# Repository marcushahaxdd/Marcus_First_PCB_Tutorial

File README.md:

# Marcus_First_PCB_Tutorial
 first try pcb

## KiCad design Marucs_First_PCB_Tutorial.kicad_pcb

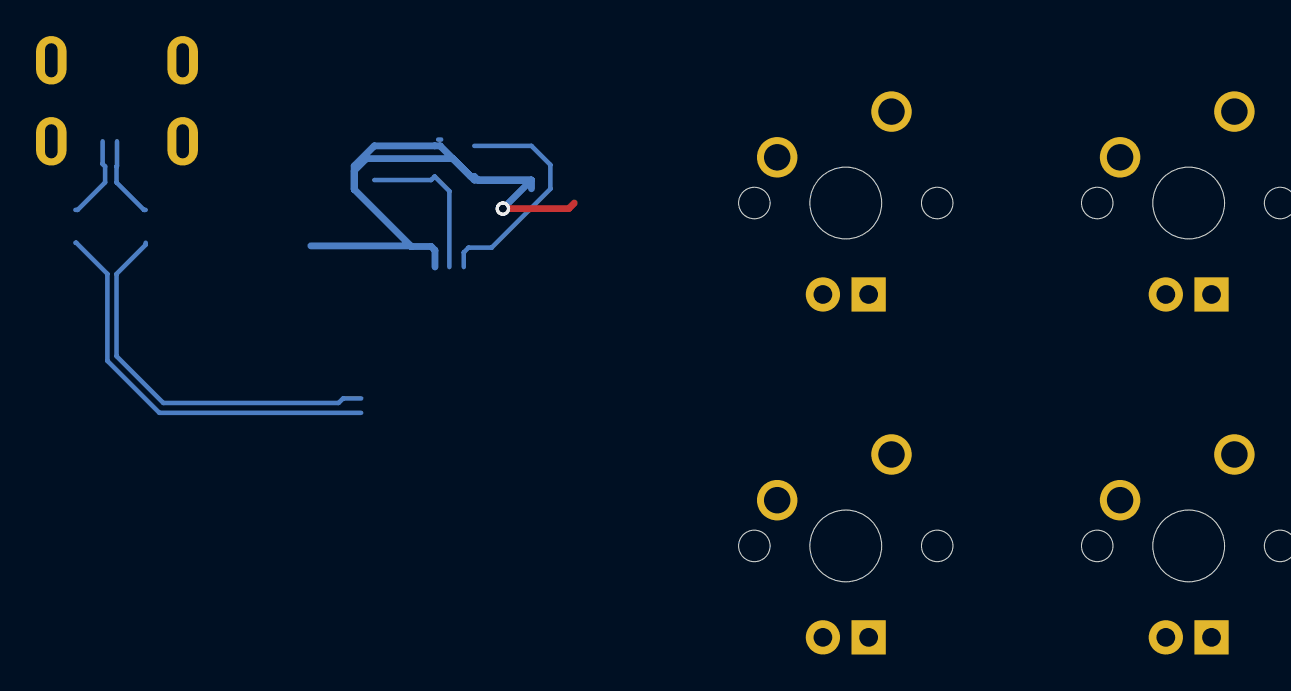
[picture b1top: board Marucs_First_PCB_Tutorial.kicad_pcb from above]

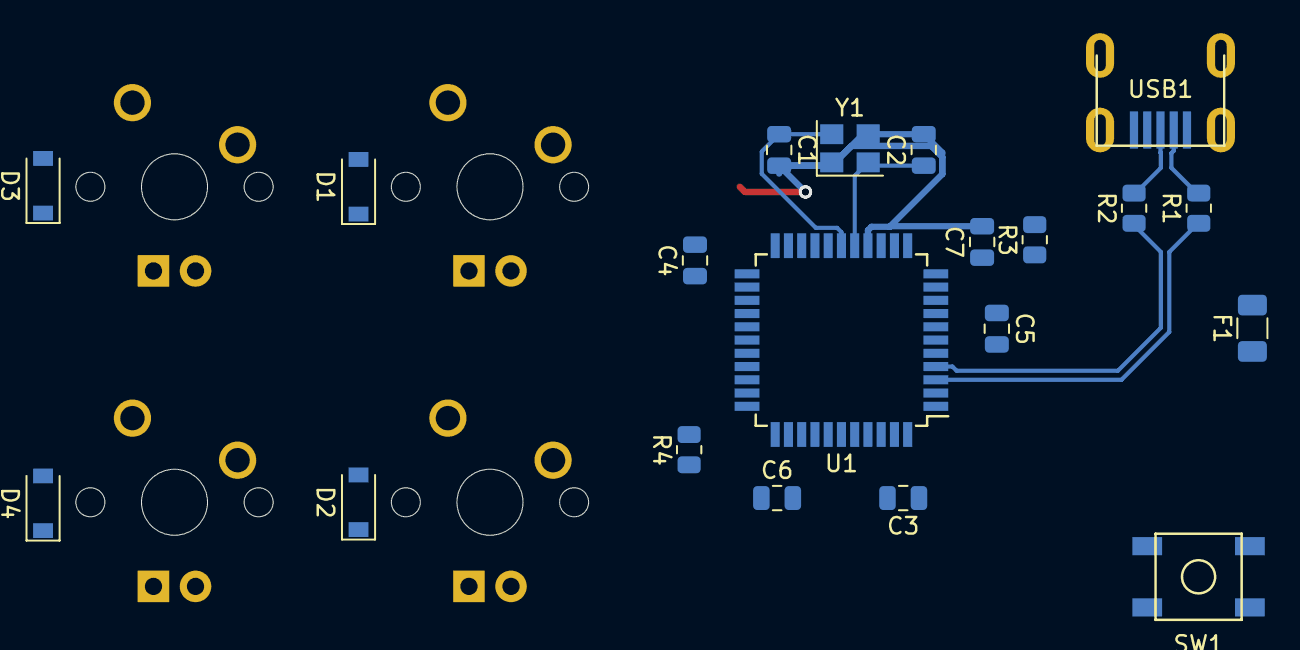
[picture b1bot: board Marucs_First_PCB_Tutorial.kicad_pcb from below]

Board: 2 copper layers, 24 parts (20 on the bottom side), 20 nets.

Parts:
C1, C2: 22pF; C_0805_2012Metric
C3: 10uF; C_0805_2012Metric
C4, C6, C7: 0.1uF; C_0805_2012Metric
C5: 1uF; C_0805_2012Metric
D1, D2, D3, D4: SOD-123; D_SOD-123
F1: 500mA; Fuse_1206_3216Metric
MX1, MX2, MX3, MX4: MX-NoLED; MXOnly-1U
R1, R2: 22; R_0805_2012Metric
R3, R4: 10k; R_0805_2012Metric
SW1: SW_Push; SKQG-1155865
U1: ATmega32U4-AU; TQFP-44_10x10mm_P0.8mm
USB1: Molex-0548190589
Y1: 16MHz; Crystal_SMD_3225-4Pin_3.2x2.5mm

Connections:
+5V: C3.1, C4.1, C6.1, C7.1, F1.1, R3.1, U1.2, U1.7, U1.14, U1.24, U1.34, U1.44
COL0: MX1.1, MX2.1, U1.29
COL1: MX3.1, MX4.1, U1.28
D+: R2.2, USB1.3
D-: R1.2, USB1.4
GND: C1.2, C2.2, C3.2, C4.2, C5.2, C6.2, C7.2, R4.1, SW1.1, U1.5, U1.15, U1.23, U1.35, U1.43, USB1.1, Y1.1, Y1.3
unnamed: C1.1, U1.17, Y1.4
unnamed: C2.1, U1.16, Y1.2
unnamed: C5.1, U1.6
unnamed: D1.2, MX1.2
unnamed: D2.2, MX2.2
unnamed: D3.2, MX3.2
unnamed: D4.2, MX4.2
unnamed: R1.1, U1.3
unnamed: R2.1, U1.4
unnamed: R3.2, SW1.2, U1.13
unnamed: R4.2, U1.33
ROW0: D1.1, D3.1, U1.27
ROW1: D2.1, D4.1, U1.30
VCC: F1.2, USB1.5

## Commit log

2021-11-05 Revert "Create Marcus_First_PCB_Tutorial.pro"
    This reverts commit 1266b2a19506ef8909f10e395839e1bf4645765a.
2021-11-05 Revert "Create Marcus_First_PCB_Tutorial.kicad_pcb"
    This reverts commit a8f711c52ef5710d59e0163757876ef50258211e.
2021-11-05 Revert "Create Marcus_First_PCB_Tutorial.sch"
    This reverts commit 035df56a3619d0889ceb0ebbcb8310dc405cb9f2.
2021-11-06 Add submodules
2021-11-07 Create fp-lib-table
2021-11-07 Create sym-lib-table
2021-11-07 Create fp-info-cache
2021-11-07 Create Marucs_First_PCB_Tutorial.sch-bak
2021-11-07 Update Marucs_First_PCB_Tutorial.sch-bak
2021-11-07 Create Marucs_First_PCB_Tutorial.kicad_pcb-bak
2021-11-07 Update Marucs_First_PCB_Tutorial.kicad_pcb-bak
